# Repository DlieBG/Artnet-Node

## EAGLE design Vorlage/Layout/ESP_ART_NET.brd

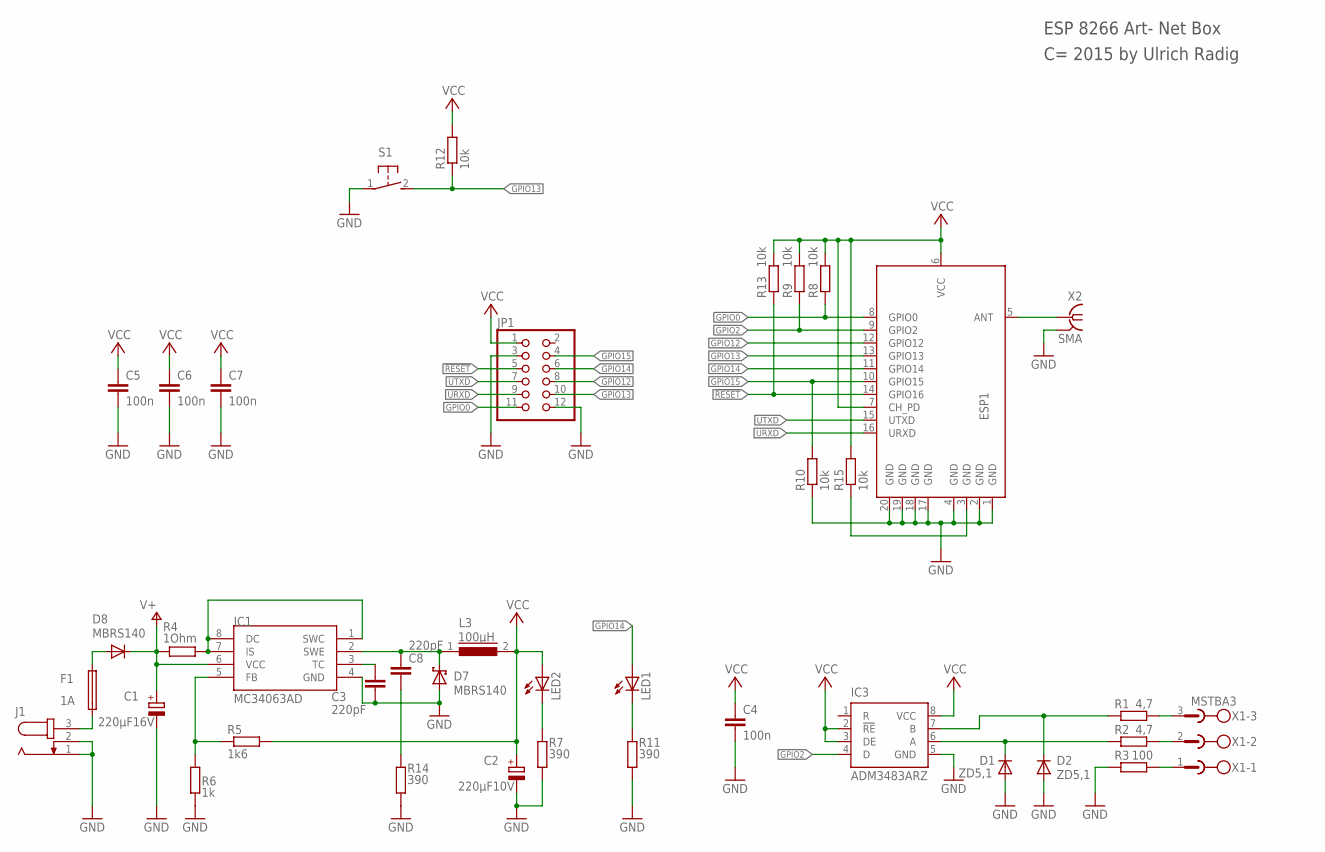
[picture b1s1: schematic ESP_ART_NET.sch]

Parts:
C1: 220µF16V; E5-8,5
C2: 220µF10V; E2,5-7
C3, C8: 220pF; C0805
C4, C5, C6, C7: 100n; C0805
D1, D2: ZD5,1; SOD80C
D7, D8: MBRS140; SMB
ESP1: ESP8266MOD
F1: 1A; PICOFUSE
IC1: MC34063AD; SOIC8
IC3: ADM3483ARZ; SO-08
J1: JACK-PLUG1; SPC4078
JP1: PINHD-2X6; 2X06
L3: 100µH; SLF7045
LED1, LED2: LEDCHIPLED_1206; CHIPLED_1206
R1, R2: 4,7; R0805
R3: 100; R0805
R4: 1Ohm; 0207/10
R5: 1k6; M0805
R6: 1k; M0805
R7, R11, R14: 390; R0805
R8, R9, R10, R12, R13, R15: 10k; R0805
S1: 31-XX; B3F-31XX
X1: MSTBA3
X2: SMA; J502-ND-142-0701-801/806

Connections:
!RESET: ESP1.14 (GPIO16), JP1.5, R13.1
GND: C1.-, C2.-, C3.2, C4.2, C5.2, C6.2, C7.2, D1.A, D2.A, D7.A, ESP1.1 (GND), ESP1.2 (GND), ESP1.4 (GND), ESP1.17 (GND), ESP1.18 (GND), ESP1.19 (GND), ESP1.20 (GND), IC1.4 (GND), IC3.5 (GND), J1.1, J1.2, JP1.3, JP1.12, R3.1, R6.1, R7.1, R10.1, R11.1, R14.1, S1.1, X2.G@1 (GND), X2.G@2 (GND), X2.G@3 (GND), X2.G@4 (GND)
GPIO0: ESP1.8 (GPIO0), JP1.11, R8.1
GPIO2: ESP1.9 (GPIO2), IC3.4 (D), R9.1
GPIO12: ESP1.12 (GPIO12), JP1.8
GPIO13: ESP1.13 (GPIO13), JP1.10, R12.1, S1.2 (S)
GPIO14: ESP1.11 (GPIO14), JP1.6, LED1.A
GPIO15: ESP1.10 (GPIO15), JP1.4, R10.2
unnamed: LED2.C, R7.2
unnamed: ESP1.5 (ANT), X2.1
unnamed: LED1.C, R11.2
unnamed: D1.C, IC3.6 (A), R2.1
unnamed: D2.C, IC3.7 (B), R1.1
unnamed: R3.2, X1.1
unnamed: R2.2, X1.2
unnamed: R1.2, X1.3
unnamed: C8.2, R14.2
unnamed: ESP1.3 (GND), R15.1
unnamed: IC1.5 (FB), R5.1, R6.2
unnamed: C3.1, IC1.3 (TC)
unnamed: IC1.1 (SWC), IC1.7 (IS), IC1.8 (DC), R4.2
unnamed: C8.1, D7.C, IC1.2 (SWE), L3.1
unnamed: D8.A, F1.2
unnamed: F1.1, J1.3
URXD: ESP1.16 (URXD), JP1.9
UTXD: ESP1.15 (UTXD), JP1.7
V+: C1.+, D8.C, IC1.6 (VCC), R4.1
VCC: C2.+, C4.1, C5.1, C6.1, C7.1, ESP1.6 (VCC), ESP1.7 (CH_PD), IC3.2 (!RE), IC3.3 (DE), IC3.8 (VCC), JP1.1, L3.2, LED2.A, R5.2, R8.2, R9.2, R12.2, R13.2, R15.2

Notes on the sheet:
C= 2015 by Ulrich Radig
ESP 8266 Art- Net Box

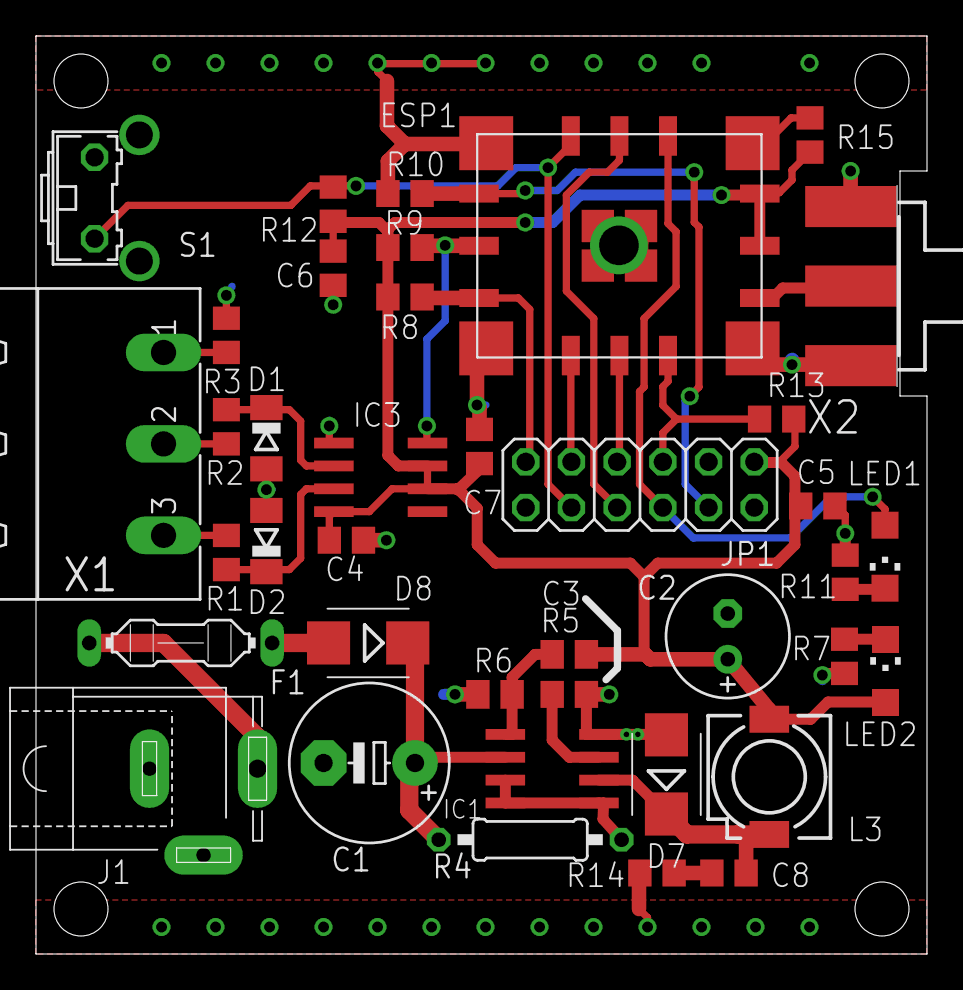
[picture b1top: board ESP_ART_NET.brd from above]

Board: 2 copper layers, 49.5 x 51.0 mm, 39 parts (0 on the bottom side), 28 nets.

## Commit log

2020-07-25 Alte Software
2020-07-26 Create LICENSE
2020-08-12 ADmin ESP8266
2020-08-12 html
2023-12-15 Add renovate.json
